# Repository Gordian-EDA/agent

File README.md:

# Gordian

An LLM agent that designs **KiCad schematics and PCBs** from a natural-language prompt.

You describe a circuit and the agent produces a real `.kicad_sch` schematic and, when asked, a
routed `.kicad_pcb` board — validated against KiCad's own ERC/DRC.

## The idea

The model never emits coordinates or copper. It describes the circuit as a **netlist** (parts,
values, footprints, and the net every pin connects to) plus **layout trees** — a CSS-flexbox-like
`row`/`col` tree of parts per functional block. A deterministic engine turns that into an exact
drawing: it places parts, routes wires, adds labels and power symbols, compiles a real
`.kicad_sch`, and reports connectivity/geometry issues back to the model. The same split carries
through to the board: schematic accepted -> deterministic placement + Freerouting + KiCad DRC
produce the `.kicad_pcb`, with no further model involvement.

This keeps the drawing reproducible and correct while the model handles the open-ended part of
design: part selection, pin mapping, and composing a block that looks like a human drew it.

### The seven tools

The design loop (`crates/gordian-core/src/tools.rs`) drives exactly seven tools:

| Tool | Purpose |
|------|---------|
| `search_symbols` | Search KiCad's stock symbol libraries by part number, function, or lib prefix |
| `symbol_info` | Pin table (number, name, electrical type, side) of a symbol, per unit |
| `build` | Lay out + compile the netlist and layout trees into `.kicad_sch`; fast, no KiCad, no image |
| `erc` | Run KiCad ERC on the last build |
| `render` | Render the last build with a coordinate grid, for the model to inspect |
| `review` | Independent visual critic: score 1-10 against a reference sheet, plus a defect list |
| `finish` | Deliver the last build, gated on a clean build, ERC with no errors, and a review >= 8 |

Editing an existing sheet swaps `build`'s argument for a **patch** (`remove`/`update`/`add`)
against the live design instead of a whole new one; the model gets the current design as JSON with
stable ids on every element so it can scope a change precisely.

Once a build is accepted, the composition polish pass (`compose`) may revise only the layout trees
against the critic's defects — the netlist is frozen, so a round can only improve the drawing.

## Skills

`skills/<name>/SKILL.md` files hold a verified parts list, pin map, and ready-to-build design JSON
for one well-known circuit family (e.g. a Blue Pill). `gordian-skills` selects up to two skills
against the prompt — a deterministic trigger-keyword pass, then `fuzzy-matcher`'s `SkimMatcherV2`
ranking of the prompt against each skill's triggers and name — and rides the match with the
opening message, framed as a starting point the model should adapt rather than a fixed answer.

## The PCB stage

Once the schematic is accepted, `pcb-auto` builds the board deterministically from the same
netlist: it sizes an outline at human courtyard density, seats connectors on the edges, places the
rest by connectivity, pours a ground zone, routes with a headless **Freerouting** (bundled at
`vendor/freerouting.jar`, driven as a subprocess), and gates the result on KiCad's own DRC. Nothing
here calls the model; it runs concurrently with the schematic's composition polish pass and starts
as soon as the first clean build exists, since a change of *drawing* is not necessarily a change of
*netlist*.

## Quick start

Requires:

- A recent **Rust** toolchain (edition 2024, rustc >= 1.85).
- **KiCad 10** (only KiCad 10 or newer is supported) — for its symbol/footprint libraries and
  `kicad-cli` (ERC, DRC, render, fabrication export).
- **Java 25** on `PATH` — Freerouting is a JVM router, invoked headless by `pcb-auto`.

```sh
cargo build --release

# First run creates the platform config file, e.g. ~/.config/gordian/config.toml,
# from config.example.toml. Set llm.model and llm.apiKey there.

# Design a schematic and route its board:
cargo run --release -p gordian -- agent --project ./my_board "a 3.3V buck converter from 12V, 2A"

# Schematic only:
cargo run --release -p gordian -- agent --project ./my_board --no-pcb "..."
```

`gordian agent --help` lists the rest: `--budget <seconds>` (wall clock for the whole run),
`--max-builds <n>` (ceiling on `build` calls), `--no-review` (skip the composition polish pass).
Editing an existing project re-runs the same command against a directory that already holds a
schematic; the model receives it as a patch target instead of starting from a blank sheet.

## Configuration

Gordian reads/writes `~/.config/gordian/config.toml` (`gordian-runtime::platform::config_path`).
`config.example.toml` documents every key the config model
(`crates/gordian-runtime/src/config.rs`) actually reads: `[llm]` (adapter, model, apiKey,
endpoint, maxTokens, ephemeralCache, reasoningEffort, captureReasoning, visionCapable), `[kicad]`
(optional symbolDir/footprintDir/cliPath overrides — auto-detected otherwise), `[project]`
(schematicFilename), and `[agent]` (budgetSeconds, maxBuilds; overridden by the matching CLI
flags).

## Architecture

| Crate | Role |
|-------|------|
| `gordian` | CLI entry point (`gordian agent ...`) |
| `gordian-core` | The agent: system prompt, the seven tools, the design loop, the visual critic, the composition pass, and the PCB stage glue |
| `gordian-llm` | The `Provider` seam and the `genai`-backed production LLM client |
| `gordian-runtime` | `GordianConfig`, its platform path, and process tracing |
| `gordian-skills` | `skills/<name>/SKILL.md` loading and fuzzy selection against a prompt |
| `sch-engine` | The deterministic schematic engine: netlist + layout trees -> laid out, compiled `.kicad_sch`, checked |
| `pcb-auto` | Deterministic PCB auto-layout: outline, placement, Freerouting, ground pour, KiCad DRC |
| `kicad` | KiCad installation discovery and typed `kicad-cli` operations (ERC/DRC, render, netlist, fab export) |
| `kicad-symbol` | `.kicad_sym` library reader, pin metadata, symbol drawing geometry, search |
| `kicad-footprint` | `.pretty` footprint library reader, pad/courtyard geometry, search |
| `geom` | Leaf math shared across the schematic and PCB stacks (2-D shapes, grid snapping, deterministic ids) |
| `quality-facts` | `sch_facts`/`pcb_facts` binaries: deterministic facts about a `.kicad_sch`/`.kicad_pcb` for the quality harness |

## Testing

```sh
cargo test --workspace --quiet
cargo clippy --workspace --all-targets -- -D warnings
cargo fmt --all -- --check
```

### Quality harness

`quality/run.py` runs end-to-end create/edit prompts through the real agent and scores the result:
deterministic facts first (`quality-facts`, KiCad ERC/DRC), then a VLM judge second. A failed
deterministic check caps the score regardless of what the judge thought.

```sh
python3 quality/run.py --list
python3 quality/run.py --suite schematic --jobs 2 --output quality/runs/schematic
python3 quality/run.py --question "is the board production-ready?" create-hard-pcb
```

Suites: `schematic` (`dataset-*` + `prompt-*`), `campaign` (end-to-end schematic+PCB), `pcb`, `all`.
`--jobs N` runs N cases at a time; `--repeat N` runs each case N times and reports the median (a
single VLM read has real run-to-run variance).

The runner uses `llm.endpoint`/`llm.apiKey`/`llm.model` from the platform config, same as a normal
agent run, and KiCad checks/reference renders use `KICAD_CLI` or `kicad.cliPath` from it — only
KiCad 10 is accepted. `tools/schematic_critic.py` and `tools/pcb_critic.py` are the two VLM
critics `quality/run.py` shells out to for the judge pass; `gordian-core::critic` embeds the same
rubric text (`tools/schematic_critic_*.txt`) so the agent's own in-loop `review` tool grades a
sheet by the identical standard.

## License

Licensed under the [Apache License, Version 2.0](LICENSE).

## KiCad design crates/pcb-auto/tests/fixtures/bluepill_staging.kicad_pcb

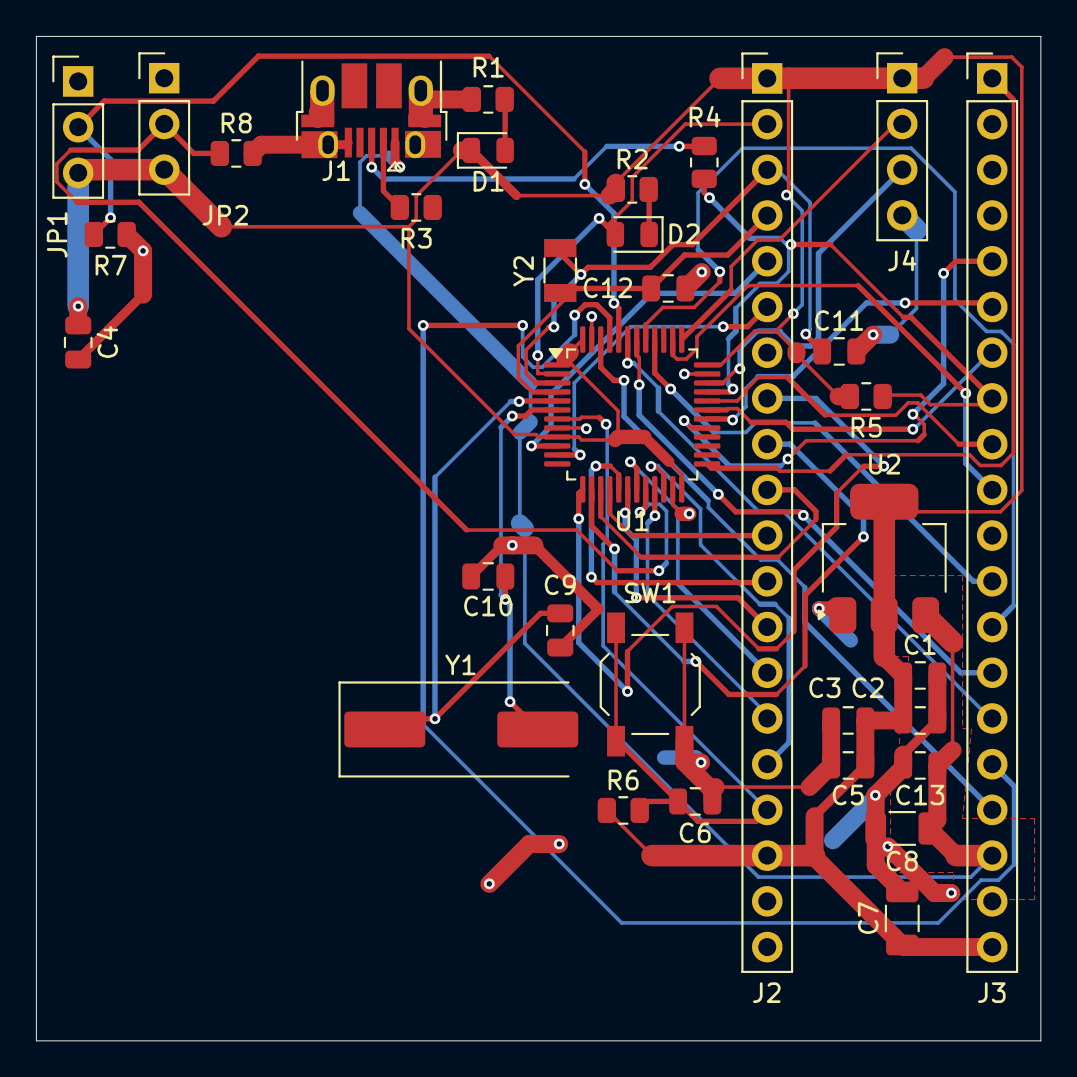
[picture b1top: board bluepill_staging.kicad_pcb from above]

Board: 2 copper layers, 55.8 x 55.8 mm, 34 parts (0 on the bottom side), 46 nets.

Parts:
C1, C2, C3, C4, C5, C6, C13: 100nF; C_0805_2012Metric
C7, C8: 10uF; C_1206_3216Metric
C9, C10: 20pF; C_0805_2012Metric
C11, C12: 12pF; C_0805_2012Metric
D1: PWR; LED_0805_2012Metric
D2: PC13; LED_0805_2012Metric
J1: USB_B_Micro; USB_Micro-B_Amphenol_10103594-0001LF_Horizontal
J2, J3: Conn_01x20; PinHeader_1x20_P2.54mm_Vertical
J4: SWD; PinHeader_1x04_P2.54mm_Vertical
JP1: BOOT0; PinHeader_1x03_P2.54mm_Vertical
JP2: BOOT1; PinHeader_1x03_P2.54mm_Vertical
R1, R2: 1k; R_0805_2012Metric
R3, R4: 22R; R_0805_2012Metric
R5: 1k5; R_0805_2012Metric
R6, R7, R8: 10k; R_0805_2012Metric
SW1: RESET; SW_SPST_TL3342
U1: STM32F103C8T6; LQFP-48_7x7mm_P0.5mm
U2: AMS1117-3.3; SOT-223-3_TabPin2
Y1: 8MHz; Crystal_SMD_HC49-SD
Y2: 32.768kHz; Crystal_SMD_3215-2Pin_3.2x1.5mm

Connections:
+3V3: C1.1, C2.1, C3.1, C4.1, C5.1, C7.1, D1.1, J2.1, J2.18, J3.20, J4.1, JP1.3, JP2.3, R2.1, R5.1, R6.1, U1.1, U1.9, U1.24, U1.36, U1.48, U2.2
+5V: C8.1, C13.1, J1.1, J3.18, U2.3
BOOT0: JP1.2, R7.1, U1.44
BOOT1: JP2.2, R8.1, U1.20
GND: C1.2, C2.2, C3.2, C4.2, C5.2, C6.2, C7.2, C8.2, C9.2, C10.2, C11.2, C12.2, C13.2, J1.5, J1.SH, J2.19, J2.20, J3.19, J4.4, JP1.1, JP2.1, R1.2, R7.2, R8.2, SW1.2, U1.8, U1.23, U1.35, U1.47, U2.1
LED_PWR: D1.2, R1.1
LED_USR: D2.1, R2.2
NRST: C6.1, J2.17, R6.2, SW1.1, U1.7
OSC32_IN: C11.1, J2.3, U1.3, Y2.1
OSC32_OUT: C12.1, J2.4, U1.4, Y2.2
OSC_IN: C9.1, U1.5, Y1.1
OSC_OUT: C10.1, U1.6, Y1.2
PA0: J2.5, U1.10
PA1: J2.6, U1.11
PA2: J2.7, U1.12
PA3: J2.8, U1.13
PA4: J2.9, U1.14
PA5: J2.10, U1.15
PA6: J2.11, U1.16
PA7: J2.12, U1.17
PA8: J3.5, U1.29
PA9: J3.6, U1.30
PA10: J3.7, U1.31
PA15: J3.10, U1.38
PB0: J2.13, U1.18
PB1: J2.14, U1.19
PB3: J3.11, U1.39
PB4: J3.12, U1.40
PB5: J3.13, U1.41
PB6: J3.14, U1.42
PB7: J3.15, U1.43
PB8: J3.16, U1.45
PB9: J3.17, U1.46
PB10: J2.15, U1.21
PB11: J2.16, U1.22
PB12: J3.1, U1.25
PB13: J3.2, U1.26
PB14: J3.3, U1.27
PB15: J3.4, U1.28
PC13: D2.2, J2.2, U1.2
SWCLK: J4.2, U1.37
SWDIO: J4.3, U1.34
USB_DM: J1.2, R3.1
USB_DM_R: J3.9, R3.2, U1.32
USB_DP: J1.3, R4.1
USB_DP_R: J3.8, R4.2, R5.2, U1.33

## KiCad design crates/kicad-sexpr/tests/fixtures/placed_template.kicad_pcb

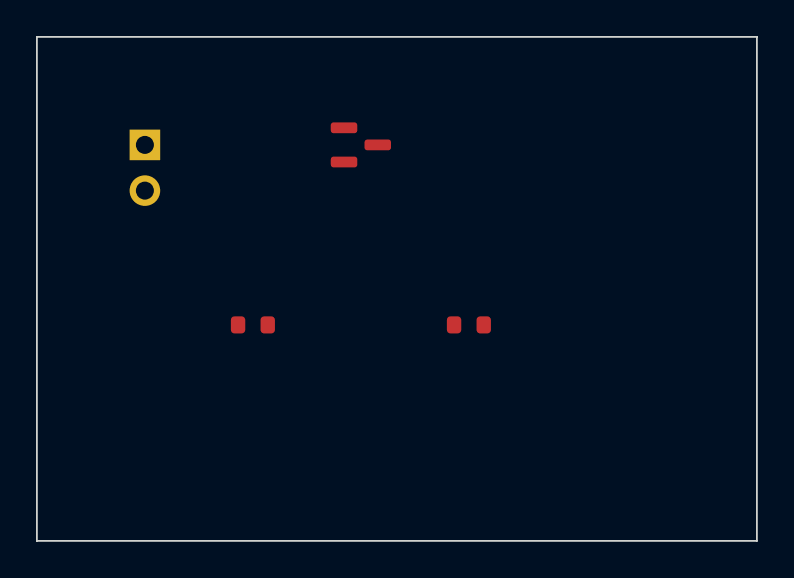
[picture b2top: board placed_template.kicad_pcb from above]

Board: 2 copper layers, 40.0 x 28.0 mm, 4 parts (0 on the bottom side), 3 nets, no tracks yet.

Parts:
J1: Conn_01x02; PinHeader_1x02_P2.54mm_Vertical
R1, R2: R; R_0603_1608Metric
U1: U; SOT-23

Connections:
GND: J1.2, R1.2, R2.2, U1.2
VIN: J1.1, U1.1
VOUT: R1.1, R2.1, U1.3

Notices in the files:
README.md:
License: Apache-2.0
